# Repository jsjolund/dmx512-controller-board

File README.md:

# Sunshine DMX512 Controller Board
Controller board for DMX512 compatible lighting fixtures, built around the ARM Cortex-M4 processor (STM32F411RET).

On the hardware side, there are of four PCB:s, a main board containing the microcontroller as well as DMX512, USB USART and power circuitry. Other boards contain buttons, LCD, potentiometer sliders and similar. See the Kicad project files for details.

The software is built using the STM32 hardware abstraction layer (HAL). Aside from hardware drivers for the various input devices, it contains DMX512 generation and a simple menu system for the LCD.

## STM32F411 docs
[Nucleo-64 board documentation](http://www.st.com/web/en/resource/technical/document/user_manual/DM00105823.pdf)

[STM32F411 Datasheet](http://www.st.com/resource/en/datasheet/stm32f411re.pdf)

[STM32F411 Reference Manual](http://www.st.com/resource/en/reference_manual/dm00119316.pdf)

[STM32F411 Programming Manual](http://www.st.com/resource/en/programming_manual/dm00046982.pdf)

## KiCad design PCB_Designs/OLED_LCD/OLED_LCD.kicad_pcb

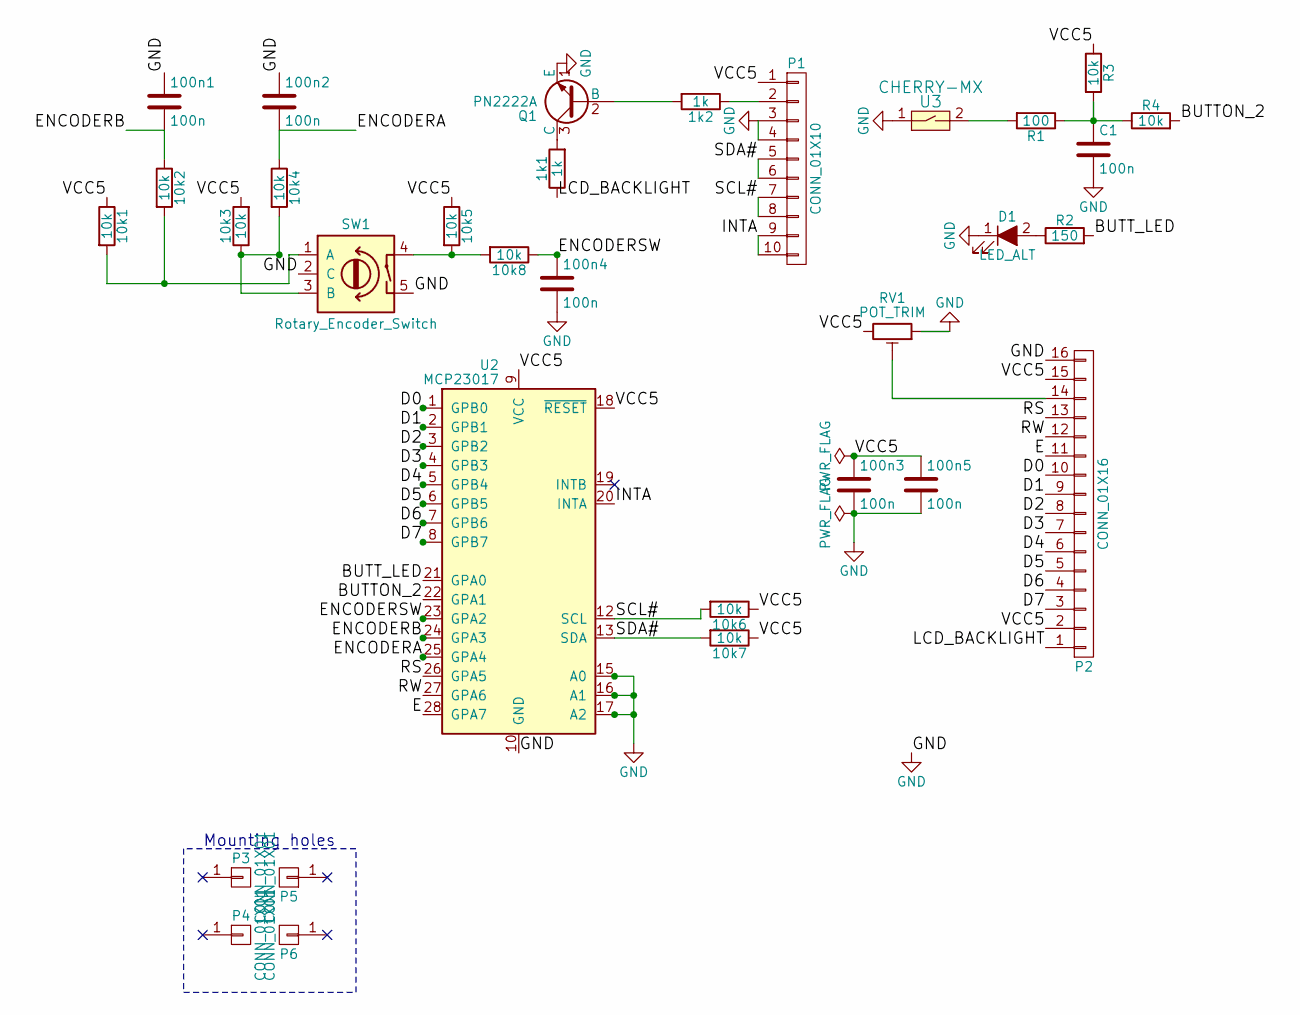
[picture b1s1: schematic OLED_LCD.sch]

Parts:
1k1, 1k2: 1k; R_0603_HandSoldering
10k1, 10k2, 10k3, 10k4, 10k5, 10k6, 10k7, 10k8: 10k; R_0603_HandSoldering
100n1, 100n2, 100n3, 100n4, 100n5: 100n; C_0603_HandSoldering
C1: 100n; C_0603_HandSoldering
D1: LED_ALT; CHERRY_MX_LED
P1: CONN_01X10; Multicomp_MC9A22-1034_2x05x2.54mm_Angled
P2: CONN_01X16; Pin_Header_Straight_1x16_Pitch2.54mm
P3, P4, P5, P6: CONN_01X01; MountingHole_2.2mm_M2_DIN965_Pad
Q1: PN2222A; TO-92_Molded_Narrow
R1: 100; R_0603_HandSoldering
R2: 150; R_0603_HandSoldering
R3, R4: 10k; R_0603_HandSoldering
RV1: POT_TRIM; Potentiometer_Trimmer_ACP_CA9v_Horizontal_Px10.0mm_Py5.0mm
SW1: Rotary_Encoder_Switch; Rotary_encoder
U2: MCP23017; SOIC-28W_7.5x17.9mm_Pitch1.27mm
U3: CHERRY-MX; CHERRY_PCB_100H

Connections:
/BUTTON_2: R4.2, U2.22 (GPA1)
/BUTT_LED: R2.2, U2.21 (GPA0)
/D0: P2.10, U2.1 (GPB0)
/D1: P2.9, U2.2 (GPB1)
/D2: P2.8, U2.3 (GPB2)
/D3: P2.7, U2.4 (GPB3)
/D4: P2.6, U2.5 (GPB4)
/D5: P2.5, U2.6 (GPB5)
/D6: P2.4, U2.7 (GPB6)
/D7: P2.3, U2.8 (GPB7)
/E: P2.11, U2.28 (GPA7)
/ENCODERA: 10k4.1, 100n2.2, U2.25 (GPA4)
/ENCODERB: 10k2.1, 100n1.2, U2.24 (GPA3)
/ENCODERSW: 10k8.1, 100n4.1, U2.23 (GPA2)
/INTA: P1.9, P1.10, U2.20 (INTA)
/LCD_BACKLIGHT: 1k1.1, P2.1
/RS: P2.13, U2.26 (GPA5)
/RW: P2.12, U2.27 (GPA6)
/SCL#: 10k6.2, P1.7, P1.8, U2.12 (SCL)
/SDA#: 10k7.2, P1.5, P1.6, U2.13 (SDA)
/VCC5: 10k1.1, 10k3.2, 10k5.1, 10k6.1, 10k7.1, 100n3.1, 100n5.1, P1.1, P2.2, P2.15, R3.1, RV1.3, U2.9 (VCC), U2.18 (~RESET)
GND: 100n1.1, 100n2.1, 100n3.2, 100n4.2, 100n5.2, C1.2, D1.1 (K), P1.3, P1.4, P2.16, Q1.1 (E), RV1.1, SW1.2 (C), SW1.5, U2.10 (GND), U2.15 (A0), U2.16 (A1), U2.17 (A2), U3.1
unnamed: 1k1.2, Q1.3 (C)
unnamed: 1k2.1, P1.2
unnamed: 1k2.2, Q1.2 (B)
unnamed: 10k1.2, 10k2.2, SW1.1 (A)
unnamed: 10k3.1, 10k4.2, SW1.3 (B)
unnamed: 10k5.2, 10k8.2, SW1.4
unnamed: C1.1, R1.1, R3.2, R4.1
unnamed: D1.2 (A), R2.1
unnamed: P2.14, RV1.2
unnamed: R1.2, U3.2

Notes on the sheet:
Mounting holes

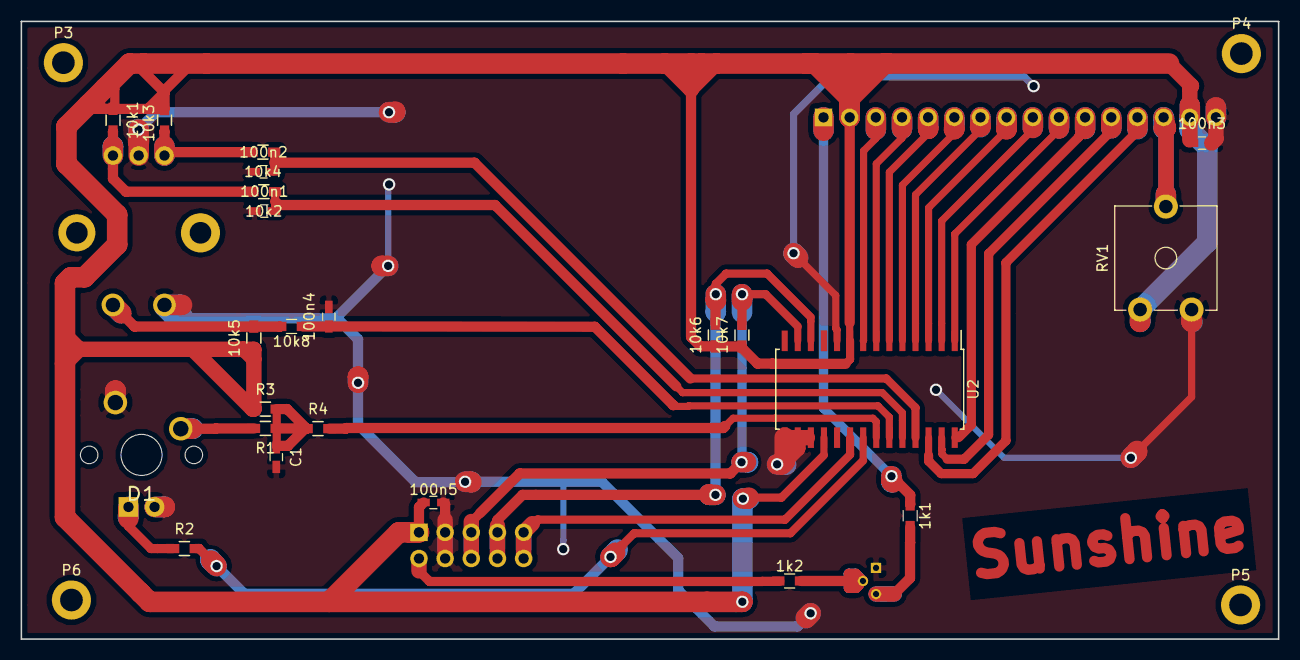
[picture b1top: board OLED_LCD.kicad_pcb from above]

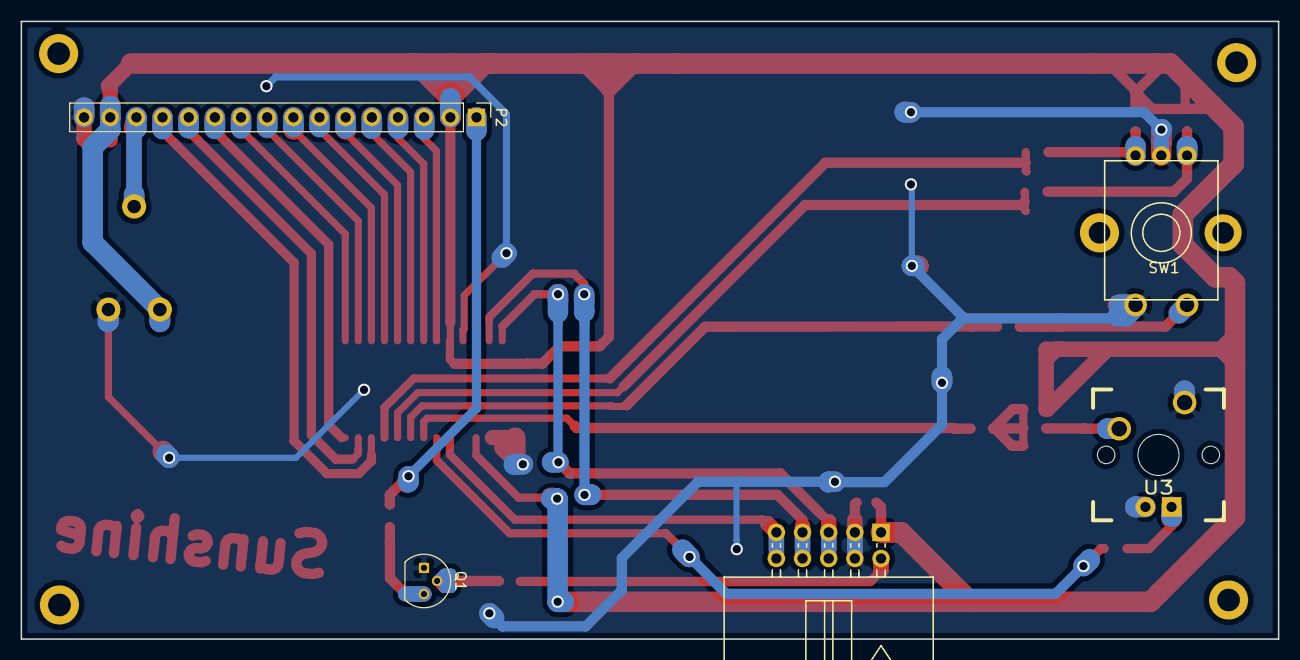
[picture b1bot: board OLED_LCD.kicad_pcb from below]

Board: 2 copper layers, 122.1 x 60.0 mm, 32 parts (6 on the bottom side), 32 nets.

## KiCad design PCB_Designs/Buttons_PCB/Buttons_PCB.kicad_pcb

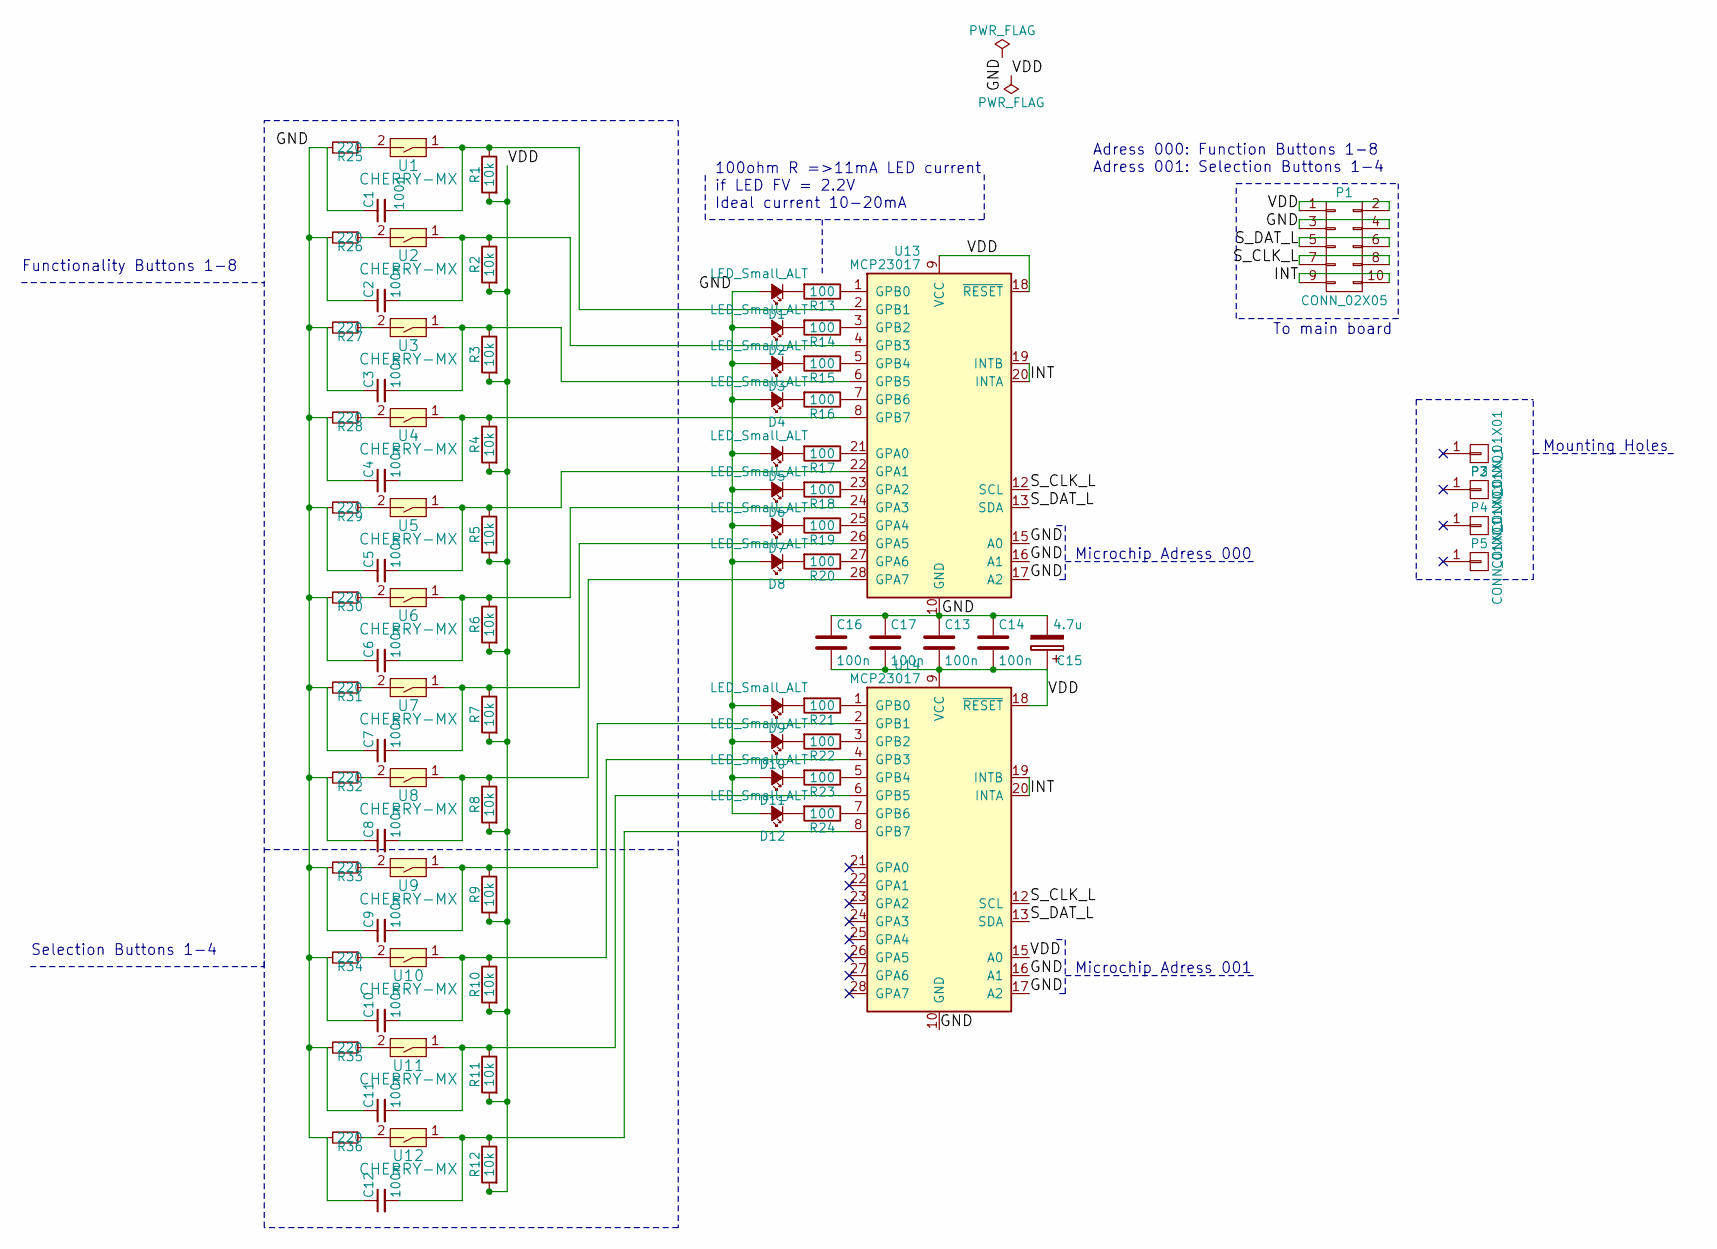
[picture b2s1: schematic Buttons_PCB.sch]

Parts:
C1, C2, C3, C4, C5, C6, C7, C8, C9, C10, C11, C12, C13, C14, C16, C17: 100n; C_0603_HandSoldering
C15: 4.7u; CP_Tantalum_Case-A_EIA-3216-18_Reflow
D1, D2, D3, D4, D5, D6, D7, D8, D9, D10, D11, D12: LED_Small_ALT; CHERRY_MX_LED
P1: CONN_02X05; Multicomp_MC9A22-1034_2x05x2.54mm_Angled
P2, P3, P4, P5: CONN_01X01; MountingHole_2.2mm_M2_DIN965_Pad
R1, R2, R3, R4, R5, R6, R7, R8, R9, R10, R11, R12: 10k; R_0603_HandSoldering
R13, R14, R15, R16, R17, R18, R19, R20, R21, R22, R23, R24: 100; R_0603_HandSoldering
R25, R26, R27, R28, R29, R30, R31, R32, R33, R34, R35, R36: 220; R_0603_HandSoldering
U1, U2, U3, U4, U5, U6, U7, U8, U9, U10, U11, U12: CHERRY-MX; CHERRY_PCB_100H
U13, U14: MCP23017; SOIC-28W_7.5x17.9mm_Pitch1.27mm

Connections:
/GND: C1.1, C2.1, C3.1, C4.1, C5.1, C6.1, C7.1, C8.1, C9.1, C10.1, C11.1, C12.1, C13.1, C14.1, C15.2, C16.1, C17.1, D1.2 (A), D2.2 (A), D3.2 (A), D4.2 (A), D5.2 (A), D6.2 (A), D7.2 (A), D8.2 (A), D9.2 (A), D10.2 (A), D11.2 (A), D12.2 (A), P1.3, P1.4, R25.2, R26.2, R27.2, R28.2, R29.2, R30.2, R31.2, R32.2, R33.2, R34.2, R35.2, R36.2, U13.10 (GND), U13.15 (A0), U13.16 (A1), U13.17 (A2), U14.10 (GND), U14.16 (A1), U14.17 (A2)
/INT: P1.9, P1.10, U13.19 (INTB), U13.20 (INTA), U14.19 (INTB), U14.20 (INTA)
/S_CLK_L: P1.7, P1.8, U13.12 (SCL), U14.12 (SCL)
/S_DAT_L: P1.5, P1.6, U13.13 (SDA), U14.13 (SDA)
/VDD: C13.2, C14.2, C15.1, C16.2, C17.2, P1.1, P1.2, R1.2, R2.2, R3.2, R4.2, R5.2, R6.2, R7.2, R8.2, R9.2, R10.2, R11.2, R12.2, U13.9 (VCC), U13.18 (~RESET), U14.9 (VCC), U14.15 (A0), U14.18 (~RESET)
unnamed: C1.2, R1.1, U1.1, U13.2 (GPB1)
unnamed: C2.2, R2.1, U2.1, U13.4 (GPB3)
unnamed: C3.2, R3.1, U3.1, U13.6 (GPB5)
unnamed: C4.2, R4.1, U4.1, U13.8 (GPB7)
unnamed: C5.2, R5.1, U5.1, U13.22 (GPA1)
unnamed: C6.2, R6.1, U6.1, U13.24 (GPA3)
unnamed: C7.2, R7.1, U7.1, U13.26 (GPA5)
unnamed: C8.2, R8.1, U8.1, U13.28 (GPA7)
unnamed: C9.2, R9.1, U9.1, U14.2 (GPB1)
unnamed: C10.2, R10.1, U10.1, U14.4 (GPB3)
unnamed: C11.2, R11.1, U11.1, U14.6 (GPB5)
unnamed: C12.2, R12.1, U12.1, U14.8 (GPB7)
unnamed: D1.1 (K), R13.2
unnamed: D2.1 (K), R14.2
unnamed: D3.1 (K), R15.2
unnamed: D4.1 (K), R16.2
unnamed: D5.1 (K), R17.2
unnamed: D6.1 (K), R18.2
unnamed: D7.1 (K), R19.2
unnamed: D8.1 (K), R20.2
unnamed: D9.1 (K), R21.2
unnamed: D10.1 (K), R22.2
unnamed: D11.1 (K), R23.2
unnamed: D12.1 (K), R24.2
unnamed: R13.1, U13.1 (GPB0)
unnamed: R14.1, U13.3 (GPB2)
unnamed: R15.1, U13.5 (GPB4)
unnamed: R16.1, U13.7 (GPB6)
unnamed: R17.1, U13.21 (GPA0)
unnamed: R18.1, U13.23 (GPA2)
unnamed: R19.1, U13.25 (GPA4)
unnamed: R20.1, U13.27 (GPA6)
unnamed: R21.1, U14.1 (GPB0)
unnamed: R22.1, U14.3 (GPB2)
unnamed: R23.1, U14.5 (GPB4)
unnamed: R24.1, U14.7 (GPB6)
unnamed: R25.1, U1.2
unnamed: R26.1, U2.2
unnamed: R27.1, U3.2
unnamed: R28.1, U4.2
unnamed: R29.1, U5.2
unnamed: R30.1, U6.2
unnamed: R31.1, U7.2
unnamed: R32.1, U8.2
unnamed: R33.1, U9.2
unnamed: R34.1, U10.2
unnamed: R35.1, U11.2
unnamed: R36.1, U12.2

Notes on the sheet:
Microchip Adress 000
Microchip Adress 001
100ohm R =>11mA LED current if LED FV = 2.2V Ideal current 10-20mA
Functionality Buttons 1-8
Selection Buttons 1-4
Adress 000: Function Buttons 1-8 Adress 001: Selection Buttons 1-4
To main board
Mounting Holes

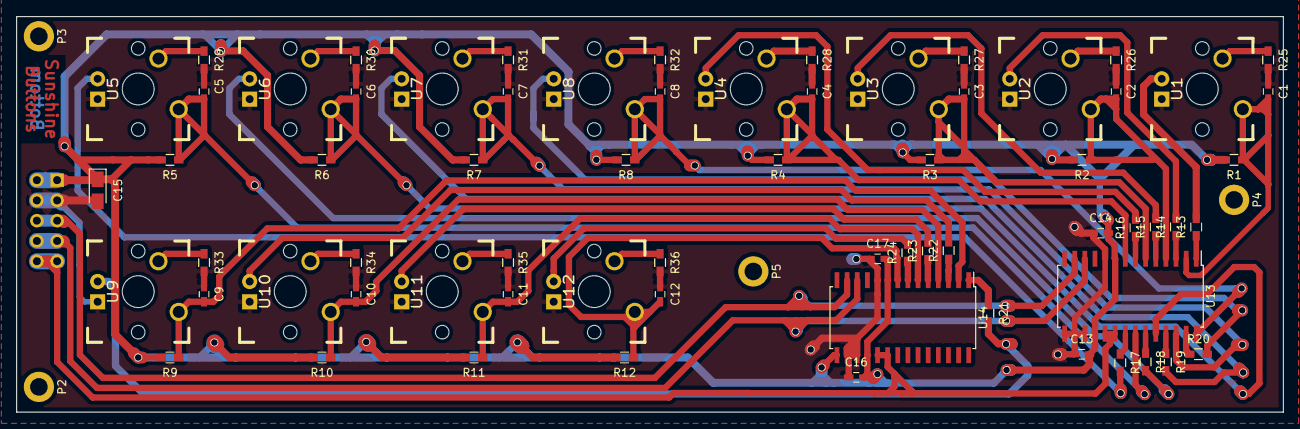
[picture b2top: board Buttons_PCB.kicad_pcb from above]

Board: 2 copper layers, 158.8 x 49.6 mm, 84 parts (1 on the bottom side), 53 nets.

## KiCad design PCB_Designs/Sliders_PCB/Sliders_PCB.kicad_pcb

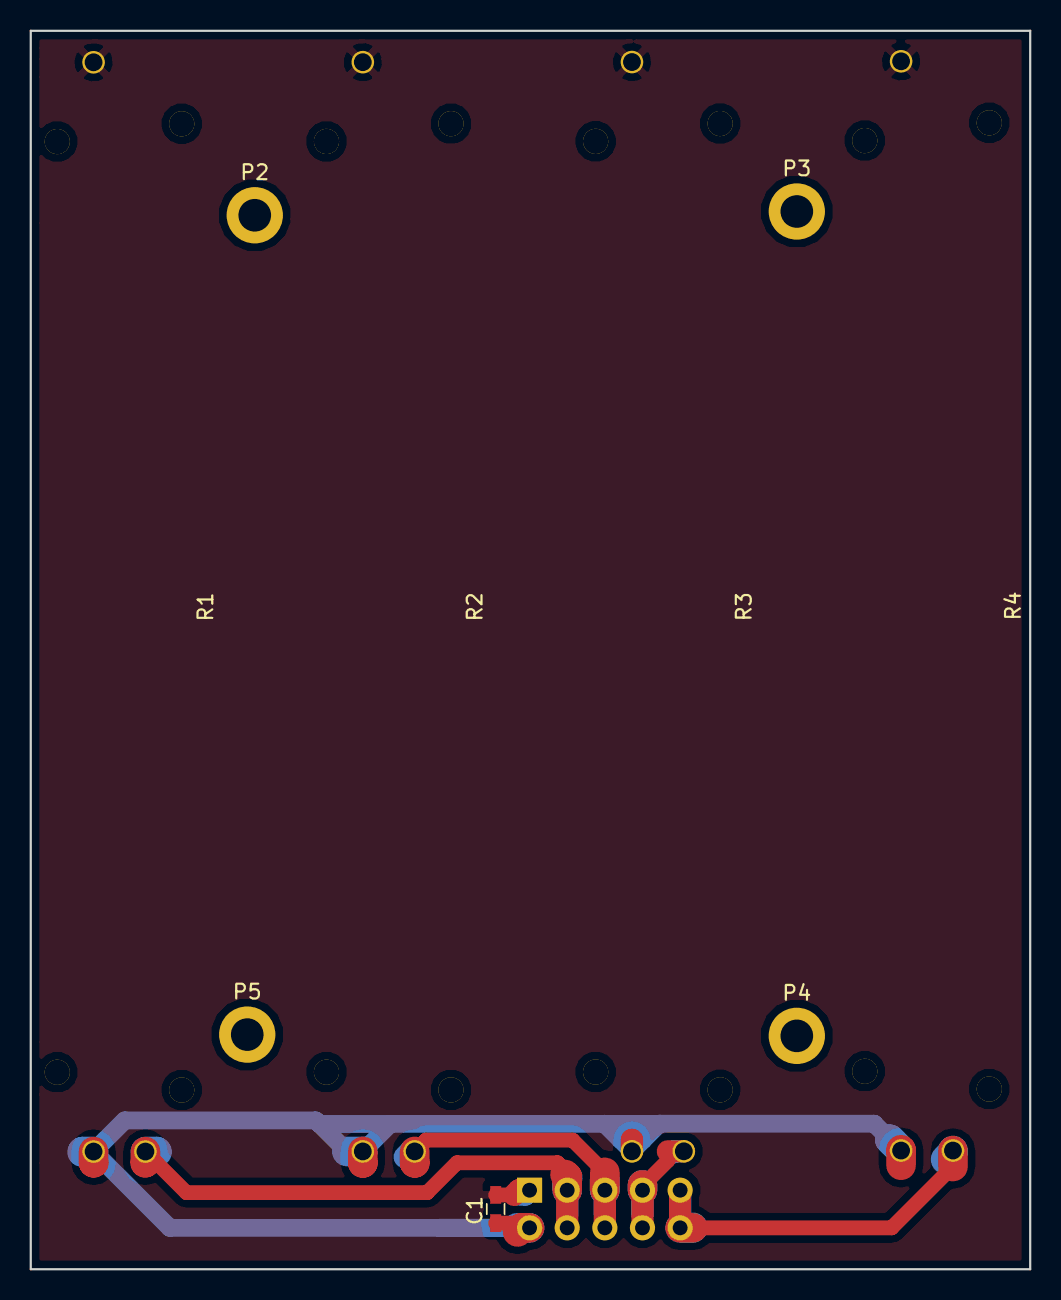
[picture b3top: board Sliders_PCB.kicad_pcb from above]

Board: 2 copper layers, 67.4 x 83.6 mm, 10 parts (1 on the bottom side), 6 nets.

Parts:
C1: 100n; C_0603_HandSoldering
P1: CONN_02X05; Multicomp_MC9A22-1034_2x05x2.54mm_Angled
P2, P3, P4, P5: CONN_01X01; MountingHole_2.2mm_M2_DIN965_Pad
R1, R2, R3, R4: PTA6043; Potentiometer_Bourns-PTA6043

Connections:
/GND: C1.2, P1.1, R1.3, R2.3, R3.3, R4.3
/VDD: C1.1, P1.2, R1.1, R2.1, R3.1, R4.1
unnamed: P1.3, P1.4, R1.2
unnamed: P1.5, P1.6, R2.2
unnamed: P1.7, P1.8, R3.2
unnamed: P1.9, P1.10, R4.2

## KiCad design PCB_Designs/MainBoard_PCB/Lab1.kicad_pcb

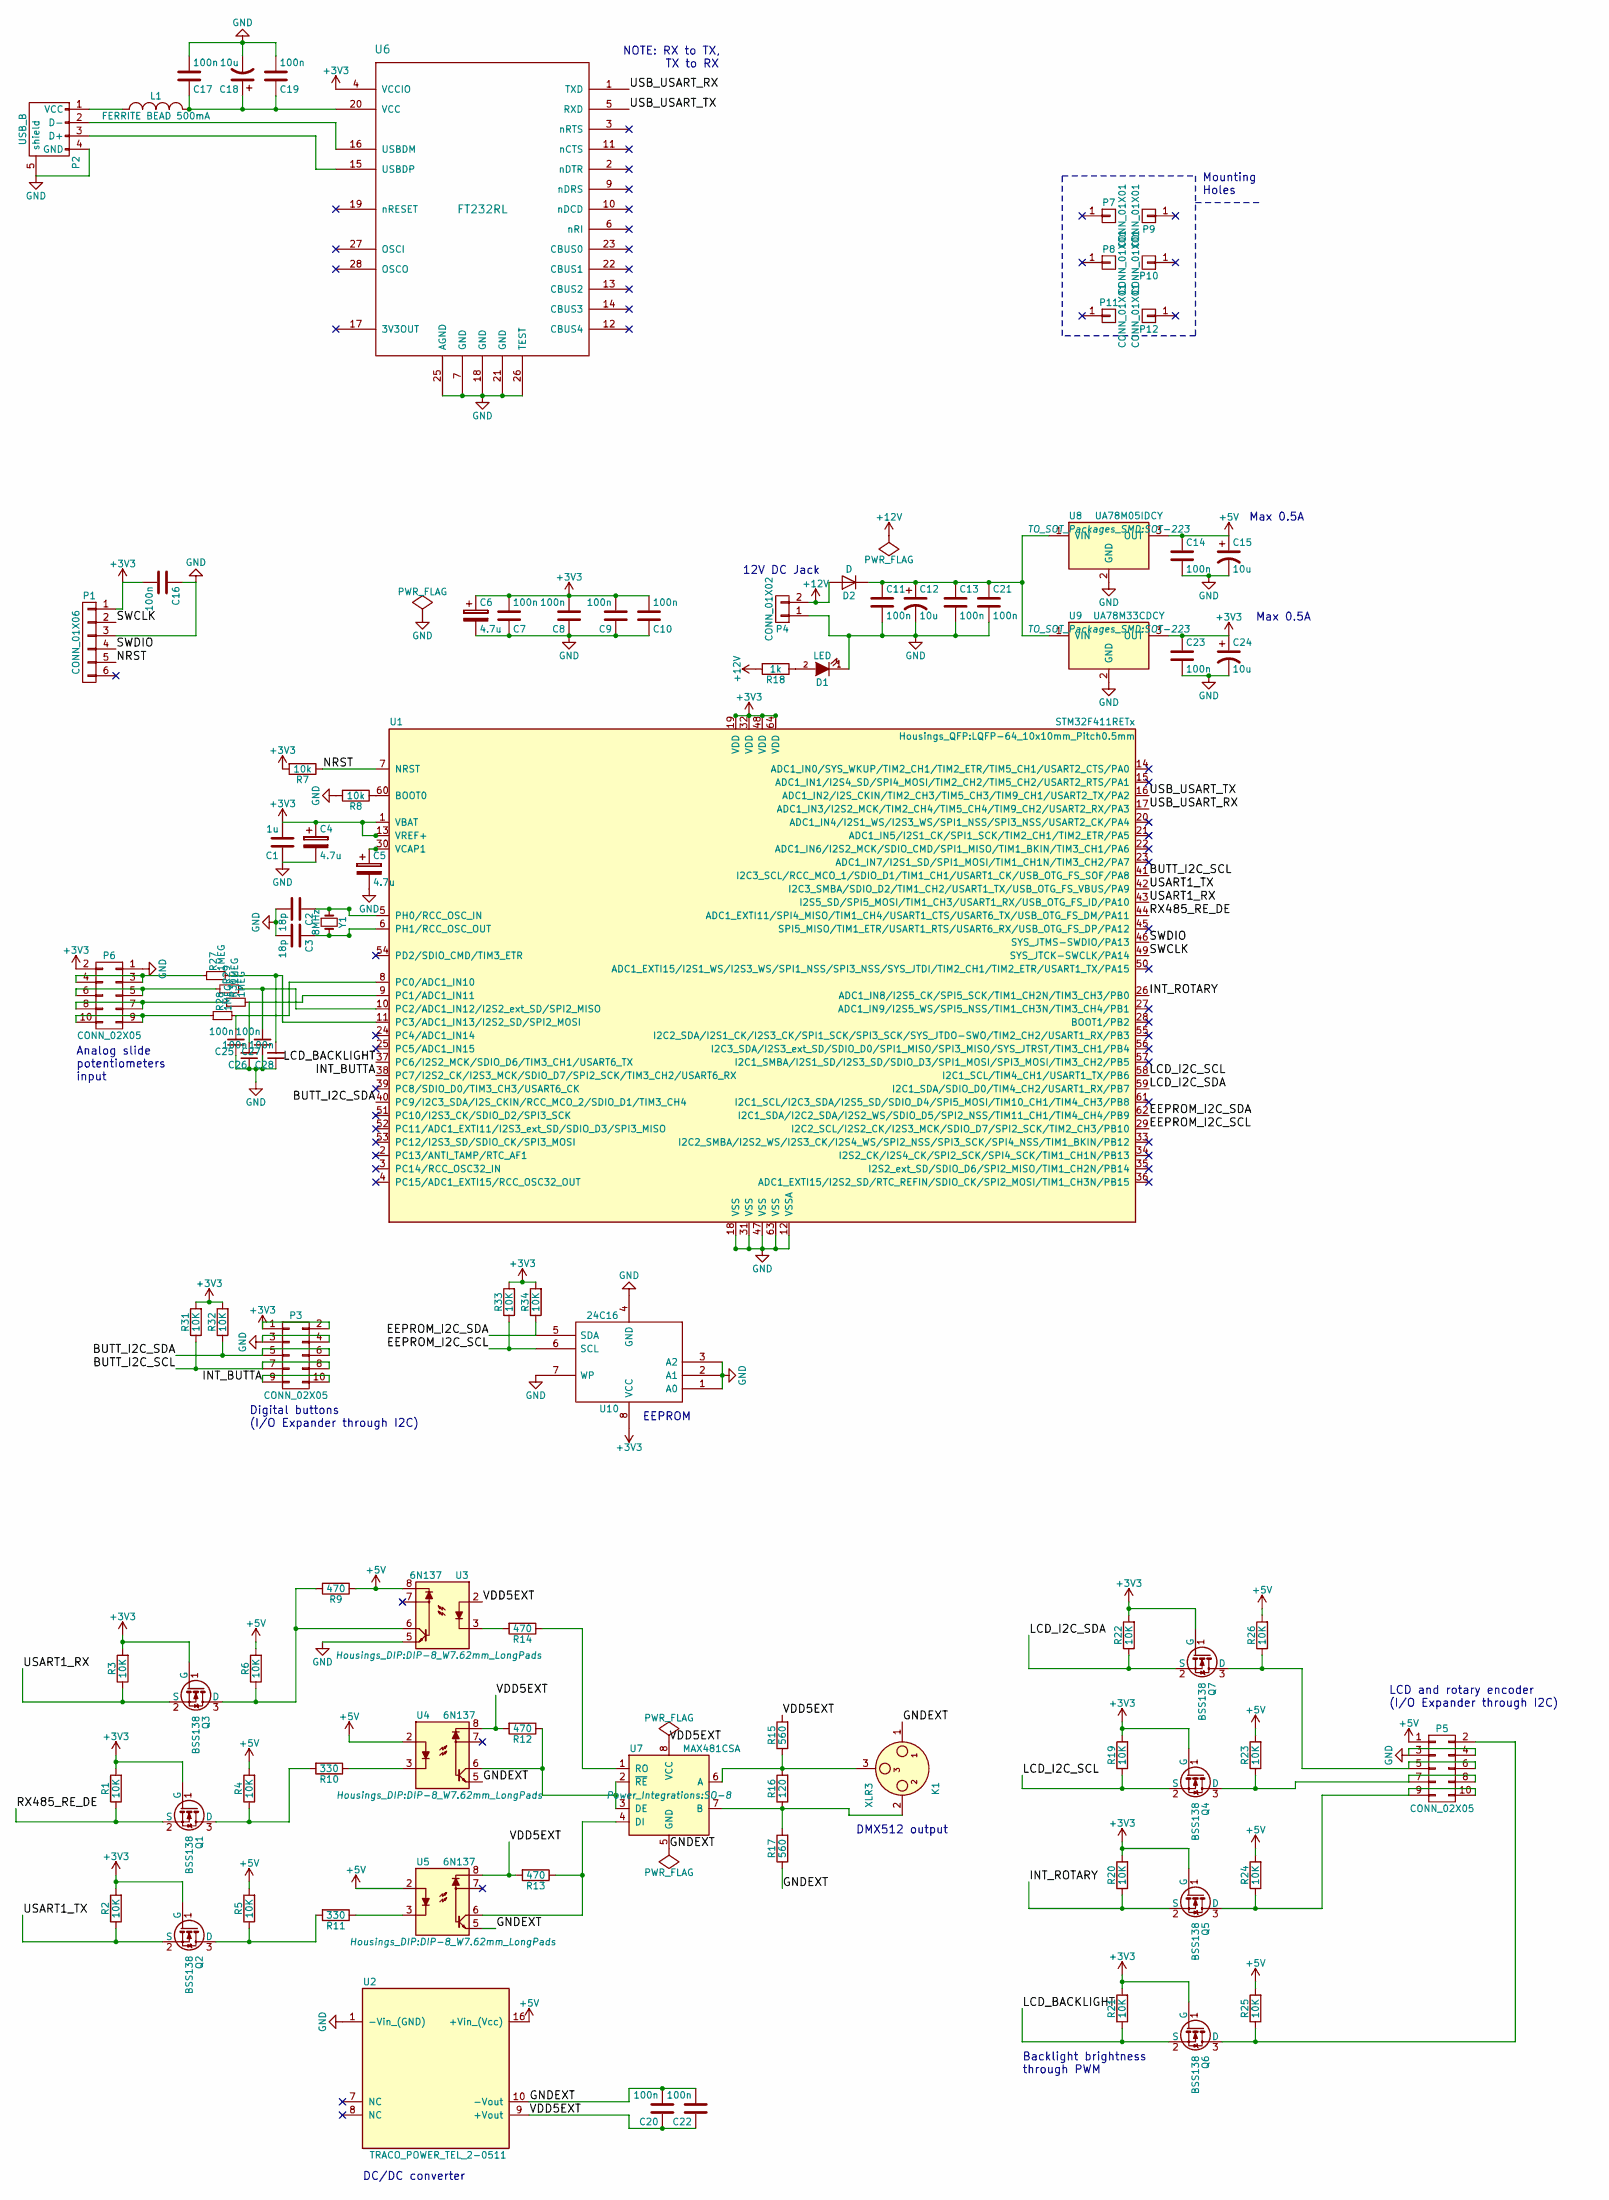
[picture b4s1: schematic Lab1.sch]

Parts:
C1: 1u; C_0603_HandSoldering
C2, C3: 18p; C_0603_HandSoldering
C4, C5, C6: 4.7u; CP_Tantalum_Case-A_EIA-3216-18_Reflow
C7, C8, C9, C10, C11, C13, C14, C16, C17, C19, C20, C21, C22, C23, C25, C26, C27, C28: 100n; C_0603_HandSoldering
C12, C15, C18, C24: 10u; CP_Tantalum_Case-A_EIA-3216-18_Reflow
D1: LED; LED_D5.0mm
D2: D; D_SOD-123
K1: XLR3; Pin_Header_Straight_1x03_Pitch1.27mm
L1: FERRITE BEAD 500mA; R_1206_HandSoldering
P1: CONN_01X06; Pin_Header_Straight_1x06_Pitch2.54mm
P2: USB_B
P3, P5, P6: CONN_02X05; Multicomp_MC9A22-1034_2x05x2.54mm_Angled
P4: CONN_01X02; Pin_Header_Straight_2x01_Pitch2.54mm
P7, P8, P9, P10, P11, P12: CONN_01X01; MountingHole_2.2mm_M2_DIN965_Pad
Q1, Q2, Q3, Q4, Q5, Q6, Q7: BSS138; SOT-23
R1, R2, R3, R4, R5, R6, R19, R20, R21, R22, R23, R24, R25, R26, R31, R32, R33, R34: 10K; R_0603_HandSoldering
R7, R8: 10k; R_0603_HandSoldering
R9, R12, R13, R14: 470; R_0603_HandSoldering
R10, R11: 330; R_0603_HandSoldering
R15, R17: 560; R_0603_HandSoldering
R16: 120; R_0603_HandSoldering
R18: 1k; R_0603_HandSoldering
R27, R28, R29, R30: 1MEG; R_0603_HandSoldering
U1: STM32F411RETx; LQFP-64_10x10mm_Pitch0.5mm
U2: TRACO_POWER_TEL_2-0511; TRACO_POWER_TEX_2-0511
U3, U4, U5: 6N137; DIP-8_W7.62mm_LongPads
U6: FT232RL; SSOP-28_5.3x10.2mm_Pitch0.65mm
U7: MAX481CSA; SO-8
U8: UA78M05IDCY; SOT-223
U9: UA78M33CDCY; SOT-223
U10: 24C16; SOIC-8_3.9x4.9mm_Pitch1.27mm
Y1: 8MHz; Crystal_SMD_HC49-SD

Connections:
+3V3: C1.2, C4.1, C6.1, C7.2, C8.2, C9.2, C10.2, C16.2, C23.1, C24.1, P1.1, P3.1, P3.2, P6.2, Q1.1 (G), Q2.1 (G), Q3.1 (G), Q4.1 (G), Q5.1 (G), Q6.1 (G), Q7.1 (G), R1.2, R2.2, R3.2, R7.2, R19.2, R20.2, R21.2, R22.2, R31.2, R32.2, R33.2, R34.2, U1.1 (VBAT), U1.13 (VREF+), U1.19 (VDD), U1.32 (VDD), U1.48 (VDD), U1.64 (VDD), U6.4 (VCCIO), U9.3 (OUT), U10.8 (VCC)
+5V: C14.1, C15.1, P5.1, R4.2, R5.2, R6.2, R9.1, R23.2, R24.2, R25.2, R26.2, U2.16 (+Vin_(Vcc)), U3.8, U4.2, U5.2, U8.3 (OUT)
+12V: D2.2 (A), P4.2, R18.2
/BUTT_I2C_SCL: P3.7, P3.8, R31.1, U1.41 (I2C3_SCL/RCC_MCO_1/SDIO_D1/TIM1_CH1/USA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)
/BUTT_I2C_SDA: P3.5, P3.6, R32.1, U1.40 (PC9/I2C3_SDA/I2S_CKIN/RCC_MCO_2/SDIO_D1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)
/EEPROM_I2C_SCL: R33.1, U1.29 (I2C2_SCL/I2S2_CK/I2S3_MCK/SDIO_D7/SPI2_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), U10.6 (SCL)
/EEPROM_I2C_SDA: R34.1, U1.62 (I2C1_SDA/I2C2_SDA/I2S2_WS/SDIO_D5/SPI2_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), U10.5 (SDA)
/GNDEXT: C20.2, C22.2, K1.1, R17.1, U2.10 (-Vout), U4.5, U5.5, U7.5 (GND)
/INT_BUTTA: P3.9, P3.10, U1.38 (PC7/I2S2_CK/I2S3_MCK/SDIO_D7/SPI2_SCK/T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)
/INT_ROTARY: Q5.2 (S), R20.1, U1.26 (ADC1_IN8/I2S5_CK/SPI5_SCK/TIM1_CH2N/TIM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)
/LCD_BACKLIGHT: Q6.2 (S), R21.1, U1.37 (PC6/I2S2_MCK/SDIO_D6/TIM3_CH1/USART6_TX)
/LCD_I2C_SCL: Q4.2 (S), R19.1, U1.58 (I2C1_SCL/TIM4_CH1/USART1_TX/PB6)
/LCD_I2C_SDA: Q7.2 (S), R22.1, U1.59 (I2C1_SDA/SDIO_D0/TIM4_CH2/USART1_RX/PB7)
/NRST: P1.5, R7.1, U1.7 (NRST)
/RX485_RE_DE: Q1.2 (S), R1.1, U1.44 (ADC1_EXTI11/SPI4_MISO/TIM1_CH4/USART1_C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)
/SWCLK: P1.2, U1.49 (SYS_JTCK-SWCLK/PA14)
/SWDIO: P1.4, U1.46 (SYS_JTMS-SWDIO/PA13)
/USART1_RX: Q3.2 (S), R3.1, U1.43 (I2S5_SD/SPI5_MOSI/TIM1_CH3/USART1_RX/US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)
/USART1_TX: Q2.2 (S), R2.1, U1.42 (I2C3_SMBA/SDIO_D2/TIM1_CH2/USART1_TX/US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)
/USB_USART_RX: U1.17 (ADC1_IN3/I2S2_MCK/TIM2_CH4/TIM5_CH4/TIM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), U6.1 (TXD)
/USB_USART_TX: U1.16 (ADC1_IN2/I2S_CKIN/TIM2_CH3/TIM5_CH3/TIM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), U6.5 (RXD)
/VDD5EXT: C20.1, C22.1, R12.2, R13.2, R15.2, U2.9 (+Vout), U3.2, U4.8, U5.8, U7.8 (VCC)
GND: C1.1, C2.2, C3.2, C4.2, C5.2, C6.2, C7.1, C8.1, C9.1, C10.1, C11.2, C12.2, C13.2, C14.2, C15.2, C16.1, C17.2, C18.2, C19.2, C21.2, C23.2, C24.2, C25.1, C26.1, C27.1, C28.1, D1.1 (K), P1.3, P2.4 (GND), P2.5 (shield), P3.3, P3.4, P4.1, P5.3, P5.4, P6.1, R8.2, U1.12 (VSSA), U1.18 (VSS), U1.31 (VSS), U1.47 (VSS), U1.63 (VSS), U2.1 (-Vin_(GND)), U3.5, U6.7 (GND), U6.18 (GND), U6.21 (GND), U6.25 (AGND), U6.26 (TEST), U8.2 (GND), U9.2 (GND), U10.1 (A0), U10.2 (A1), U10.3 (A2), U10.4 (GND), U10.7 (WP)
unnamed: C2.1, U1.5 (PH0/RCC_OSC_IN), Y1.1
unnamed: C3.1, U1.6 (PH1/RCC_OSC_OUT), Y1.2
unnamed: C5.1, U1.30 (VCAP1)
unnamed: C11.1, C12.1, C13.1, C21.1, D2.1 (K), U8.1 (VIN), U9.1 (VIN)
unnamed: C17.1, C18.1, C19.1, L1.2, U6.20 (VCC)
unnamed: C25.2, R28.2, U1.8 (PC0/ADC1_IN10)
unnamed: C26.2, R30.2, U1.9 (PC1/ADC1_IN11)
unnamed: C27.2, R29.2, U1.10 (PC2/ADC1_IN12/I2S2_ext_SD/SPI2_MISO)
unnamed: C28.2, R27.2, U1.11 (PC3/ADC1_IN13/I2S2_SD/SPI2_MOSI)
unnamed: D1.2 (A), R18.1
unnamed: K1.2, R16.1, R17.2, U7.7 (B)
unnamed: K1.3, R15.1, R16.2, U7.6 (A)
unnamed: L1.1, P2.1 (VCC)
unnamed: P2.2 (D-), U6.16 (USBDM)
unnamed: P2.3 (D+), U6.15 (USBDP)
unnamed: P5.2, Q6.3 (D), R25.1
unnamed: P5.5, P5.6, Q7.3 (D), R26.1
unnamed: P5.7, P5.8, Q4.3 (D), R23.1
unnamed: P5.9, P5.10, Q5.3 (D), R24.1
unnamed: P6.3, P6.4, R27.1
unnamed: P6.5, P6.6, R29.1
unnamed: P6.7, P6.8, R30.1
unnamed: P6.9, P6.10, R28.1
unnamed: Q1.3 (D), R4.1, R10.2
unnamed: Q2.3 (D), R5.1, R11.2
unnamed: Q3.3 (D), R6.1, R9.2, U3.6
unnamed: R8.1, U1.60 (BOOT0)
unnamed: R10.1, U4.3
unnamed: R11.1, U5.3
unnamed: R12.1, U4.6, U7.2 (~RE~), U7.3 (DE)
unnamed: R13.1, U5.6, U7.4 (DI)
unnamed: R14.1, U7.1 (RO)
unnamed: R14.2, U3.3

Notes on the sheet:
NOTE: RX to TX, TX to RX
Analog slide potentiometers input
EEPROM
LCD and rotary encoder (I/O Expander through I2C)
DMX512 output
Digital buttons (I/O Expander through I2C)
12V DC Jack
Max 0.5A
Backlight brightness through PWM
DC/DC converter
Mounting Holes

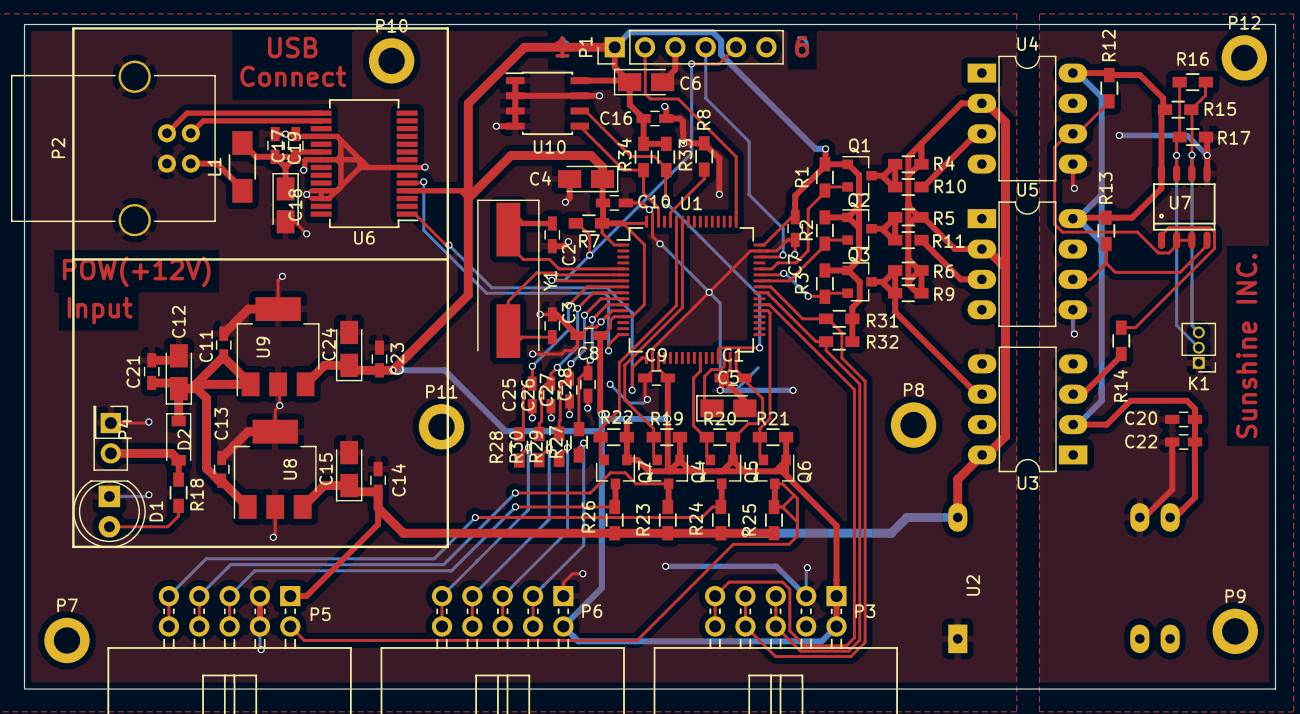
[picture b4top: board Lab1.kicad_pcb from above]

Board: 2 copper layers, 104.7 x 55.6 mm, 96 parts (0 on the bottom side), 56 nets.

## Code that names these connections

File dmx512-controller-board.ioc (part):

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Mcu.Name=STM32F411R(C-E)Tx
Mcu.Package=LQFP64
Mcu.UserName=STM32F411RETx
PA10.GPIOParameters=GPIO_Label
PA10.GPIO_Label=DMX_RX
PA10.Mode=Asynchronous
PA10.Signal=USART1_RX
PA11.GPIOParameters=PinState,GPIO_Label
PA11.GPIO_Label=DMX_EN
PA11.PinState=GPIO_PIN_SET
PA11.Signal=GPIO_Output
PA13.GPIOParameters=GPIO_Label
PA13.GPIO_Label=TMS
PA13.Mode=Serial_Wire
PA13.Signal=SYS_JTMS-SWDIO
PA14.GPIOParameters=GPIO_Label
PA14.GPIO_Label=TCK
PA14.Mode=Serial_Wire
PA14.Signal=SYS_JTCK-SWCLK
PA2.GPIOParameters=GPIO_Label
PA2.GPIO_Label=USB_TX
PA2.Mode=Asynchronous
PA2.Signal=USART2_TX
PA3.GPIOParameters=GPIO_Label
PA3.GPIO_Label=USB_RX
PA3.Mode=Asynchronous
PA3.Signal=USART2_RX
PA5.GPIOParameters=GPIO_Label
PA5.GPIO_Label=LD2 [Green Led]
PA5.Signal=GPIO_Output
PA8.GPIOParameters=GPIO_Label
PA8.GPIO_Label=BUTTONS_SCL
PA8.Mode=I2C
PA8.Signal=I2C3_SCL
PA9.GPIOParameters=GPIO_Label
PA9.GPIO_Label=DMX_TX
PA9.Mode=Asynchronous
PA9.Signal=USART1_TX
PB0.GPIOParameters=GPIO_Label,GPIO_ModeDefaultEXTI
PB0.GPIO_Label=B0 [RotEnc INT0]
PB0.GPIO_ModeDefaultEXTI=GPIO_MODE_IT_RISING_FALLING
PB0.Signal=GPXTI0
PB10.GPIOParameters=GPIO_Label
PB10.GPIO_Label=EEPROM_SCL
PB10.Mode=I2C
PB10.Signal=I2C2_SCL
PB3.GPIOParameters=GPIO_Label
PB3.GPIO_Label=SWO
PB3.Signal=SYS_JTDO-SWO
PB6.GPIOParameters=GPIO_Label
PB6.GPIO_Label=LCD_SCL
PB6.Mode=I2C
PB6.Signal=I2C1_SCL
PB7.GPIOParameters=GPIO_Label
PB7.GPIO_Label=LCD_SDA
PB7.Mode=I2C
PB7.Signal=I2C1_SDA
PB9.GPIOParameters=GPIO_Label
PB9.GPIO_Label=EEPROM_SDA
PB9.Mode=I2C
PB9.Signal=I2C2_SDA
PC0.Signal=ADCx_IN10
PC1.Signal=ADCx_IN11
PC13-ANTI_TAMP.GPIOParameters=GPIO_Label,GPIO_ModeDefaultEXTI
PC13-ANTI_TAMP.GPIO_Label=B1 [Blue PushButton]
PC13-ANTI_TAMP.GPIO_ModeDefaultEXTI=GPIO_MODE_IT_FALLING
PC13-ANTI_TAMP.Signal=GPXTI13
PC14-OSC32_IN.Mode=LSE-External-Oscillator
PC14-OSC32_IN.Signal=RCC_OSC32_IN
PC15-OSC32_OUT.Mode=LSE-External-Oscillator
PC15-OSC32_OUT.Signal=RCC_OSC32_OUT
PC2.Signal=ADCx_IN12
PC3.Signal=ADCx_IN13
PC6.GPIOParameters=GPIO_Label
PC6.GPIO_Label=LCD_BL
PC6.Signal=S_TIM3_CH1
PC7.GPIOParameters=GPIO_Label,GPIO_ModeDefaultEXTI
PC7.GPIO_Label=B2 [Button INT0]
PC7.GPIO_ModeDefaultEXTI=GPIO_MODE_IT_RISING_FALLING
PC7.Signal=GPXTI7
PC9.GPIOParameters=GPIO_Label
PC9.GPIO_Label=BUTTONS_SDA
PC9.Mode=I2C
PC9.Signal=I2C3_SDA
PH0\ -\ OSC_IN.Mode=HSE-External-Oscillator
PH0\ -\ OSC_IN.Signal=RCC_OSC_IN
PH1\ -\ OSC_OUT.Mode=HSE-External-Oscillator
PH1\ -\ OSC_OUT.Signal=RCC_OSC_OUT
RCC.HSE_VALUE=8000000
RCC.SYSCLKFreq_VALUE=80000000
RCC.SYSCLKSource=RCC_SYSCLKSOURCE_PLLCLK
board=NUCLEO-F411RE
boardIOC=true

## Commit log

2017-01-25 Initial code
2017-01-25 Added STM32Cube file
2017-01-26 Added PCB Folder
    Added Custom library folder, Custom footprints folder, first schematic
    of button PCB.
2017-01-26 Added nucleo image
2017-01-26 Updated project for TrueStudio
2017-01-26 Updated .project file
2017-01-26 Added .lib slider and slider project
    stuff
2017-01-27 Slider .sch .net .brd added
    Sliders now included in project. Custom footprints and symbols for
    PTA6043 (sliders) fixed.
    Board view not finished, minor design decisions left.
2017-01-27 Code should now compile with both TrueStudio and Makefile
2017-01-27 Fixed Makefile directory problem
2017-01-28 Ignore project settings files
2017-01-28 Temporarily added -fpermissive
2017-01-28 Enable USART2
2017-01-28 USB USART transmit test
2017-01-28 Simple UART echo server
2017-01-30 Buttons PCB almost done
    * Footprints for Cherry MX switches added
    * Buttons.sch edited to finished schematic
    * Buttons.net generated
    * Buttons.kicad_pcb created and designed
    * Uneccesary files deleted
2017-01-30 stuff
2017-01-30 Allow .lib files
2017-01-30 + all .lib
    Added previous blocked .libs
2017-01-31 Buttons_PWB_1.0
    First edition Buttons_PWB routed (V1.0).
2017-02-01 Buttons_PCB v2
    Changed order of buttons 5-8 to prevent vias below SMD extenders.
2017-02-01 PTA6043, Sliders_PCB
    Added:
    PTA 6043 .lib and .pretty
    Drew traces to Sliders_PCB (v1)
2017-02-02 Sliders v2
    Sliders_PCB klara
2017-02-08 Updated MCU pins
2017-02-08 Images of used pins
2017-02-10 Main board schematic
2017-02-11 Buttons_V3, Sliders_V2
    Easier to manufacture External PCB designs finalized.
    Uneccesary footprints library added "Connectors" (Could not find the
    regular connector FP, turns out it's the socket-strips)
2017-02-12 PCB file created for main board
    Nothing really
2017-02-12 Main PCB work in progress...
2017-02-12 First PCB version of main board
2017-02-12 OLED_PCB
2017-02-14 Added 3.3v to FT232RL, use larger power tracks
2017-02-14 Fixed DC DC converter footprint
2017-02-15 Rerouted MCU pins for better Nucleo compatibility
2017-02-15 Changed rotary encoder interrupt pin
2017-02-15 Buttons V4
    Pulldown changed to pullup in button switch filter.
    Filter to switch completed (changed).
2017-02-15 LCD123
2017-02-15 Sunshine C project
    approx 40% completed
2017-02-15 update to sunshine src
    fixes
2017-02-15 Main_PCB V1 Complete
    Minor changes to everything.
    Main_PCB complete with traces and design.
2017-02-15 Completed OLED_LCD_PCB v1.1
    * Added Mountingholes.
    * Added "Fatpads" for vias (were on some but not all earlier)
    * Added bottom ground (Or etching will be a bitch)
    * Added Edge cuts (105x65mm)
2017-02-16 Added init settings
2017-02-16 Fix path problem
2017-02-16 Generated default init code
2017-02-16 USART2 DMA fix
2017-02-16 Working analog to digital project (true studio project) for sliders
    Working analog to digital project (true studio project) for the voltage readings for the analog sliders
2017-02-16 Completed all Circuits for evaluation
    * All board-to-board connectors now Multicomp 02X05
    * Mounting holes for all PCB
    * Vias at all groundpins
    * Minor other changes
2017-02-18 Working ADC with 4 Channel input in Injected Mode
    Working ADC with 4 Channel input in Injected Mode
    Pins PC0, PC1, PC2, PC3
2017-02-18 Edited Main_PCB from feedback.
    * Added RC-filter (1Mohm, 100nF)
    Little cramped now, but whatever.
    * Filled out groundplanes a little
2017-02-19 DMX512 output almost works. Can read USB->UART from Putty.
2017-02-19 Forgot to include DMX files
2017-02-19 Fixed error in Makefile
2017-02-19 Add st-util flash script
2017-02-19 USB usart now works with DMA mode
2017-02-19 Update STM32Cube file with DMA settings
2017-02-19 Changed EEPROM files to c-code
2017-02-19 Minor refactorings
2017-02-19 I2C peripherals use DMA (code generation)
2017-02-19 Minor STM32Cube file fix
2017-02-19 Forgot to include a file
2017-02-20 Added pullups for EEPROM and button I/Os
2017-02-20 WIP: EEPROM use DMA
2017-02-20 Buttons wrong IO expander footprint fixed
2017-02-20 EEPROM, USB USART and DMX now work correctly using DMA
2017-02-20 Set DMX channel values through USB COM
2017-02-21 USB control over DMX seems to work more reliably now
2017-02-22 Minor refactoring
2017-02-22 Added simple LCD library (for HD44780 chip)
2017-02-22 LCD uses TIM4 for microsecond timing
2017-02-23 Refactored lcd code
2017-02-23 Integrated ADC code. Set DMX channel values from ADC.
2017-02-24 Fixed eeprom interrupt bug
2017-02-24 Improved USART robustness (USB and DMX)
2017-02-25 Removed DMA pause/resume to avoid deadlock in DMX
2017-02-25 LCD now works with I/O expander
2017-02-25 Added Nucleo64 connector image
2017-02-25 Renamed some functions in DMX files
2017-02-25 LCD brightness fade in/out
2017-02-25 Improved command line parsing
2017-02-26 update on sys specific entry points
2017-02-26 framework update
2017-02-26 update to sysPublic and controller
2017-02-26 main updated, small header tweaks
2017-02-26 updated the logic function
2017-02-27 LCD Reset -> 5V
2017-02-27 Oled and photomasks
    * Added 1k Serie resistance to backlight in Oled LCD.
    * Created the photomasks for Buttons and Sliders.
2017-02-27 Improved DMX code and EEPROM test
2017-02-27 Integraded sunshine folder content
2017-02-27 Removed old sunshine folder
2017-02-28 Cleaned LCD code
2017-02-28 Started on buttons I/O expander
2017-02-28 Buttons work with I/O expander interrupts
2017-03-01 Nya Photomasks Buttons
2017-03-01 Edited Buttons and sliders for manufacturability
    * All vias updated to 1.5 or 2 mm diameter
    * Slight designchanges to get rid of drills close to edges in Buttons
    * New Photomasks printed for Buttons and Sliders
2017-03-02 Turn on and off button LEDs
2017-03-02 Remove permissive flag from Makefile
2017-03-02 hej2
2017-03-02 Manufacture files added
    * Gerbers created
    * Drillfiles created
    * G-CODE generated (milling information)
2017-03-03 Hotfixes, updates and Photomask
    * Edited small error in component placing (OLED_LCD)
    * Updated all photomasks in light of recent events
    * Generated photomask for OLED_LCD (.pdf)
    * Updated all Gerberfiles (.gbr)
    * Updated all drillfiles, now merging "plated" and unplated TH (.drl)
    * With merge; all Non Plated Through Hole drills deleted (-NPTH.drl)
2017-03-03 Added some comments
2017-03-05 updated main and application functions
2017-03-05 Controller update
2017-03-05 Finished Controller
2017-03-05 Fixed compilation issues and bugs
2017-03-06 Merged in some code
2017-03-07 Fixed issues with new EEPROM chip
2017-03-07 LCD code uses 20 characters width
2017-03-07 Revert accidental .cproject update
2017-03-07 Revert accidental .project update
2017-03-09 Increased DMX mark time
2017-03-09 New stuff
2017-03-12 Some work on button board and rot encoder code
2017-03-13 LCD board trim pot and transistor
2017-03-13 Working on rotary encoder stuff
2017-03-13 Minor buttons code change, print errors to LCD
2017-03-13 Add GDB flashing script from Henrik
2017-03-13 OLED new layout
    * Added few components to OLED_LCD pcb.
    * Extended PCB layout to make room for all components.
    * Generated new LCD photomasks
2017-03-13 Fix button interrupt freeze bug
2017-03-13 Minor changes to OLED
2017-03-14 Update TrueSTUDIO configs from Cube program
2017-03-14 Rotary encoder seems to work OK now
2017-03-15 Increased LCD fade on time
2017-03-15 Buttons code more readable
2017-03-15 Rotary encoder and LCD button works. Some readability improvements.
2017-03-15 Added SRP headers for memory barrier lock/unlock
2017-03-16 DMX works on actual fixtures. Improved UI and button handling.
2017-03-17 Add channel input lock, save/load from EEPROM
2017-03-18 Control unit through Freestyler, emulating Enttec Open DMX
2017-03-18 Added missing 10k R on OLED board, diodes on Buttons board
2017-03-23 Minor menu handling improvement
2017-03-23 More images
